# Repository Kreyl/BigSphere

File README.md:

# BigSphere
Hardware for big shining sphere with 70 bright LEDs

To create effects use https://github.com/notiel/SphereUI
Change arrays in EffectPulse.h and EffectStrobo.h to generated by effect creator

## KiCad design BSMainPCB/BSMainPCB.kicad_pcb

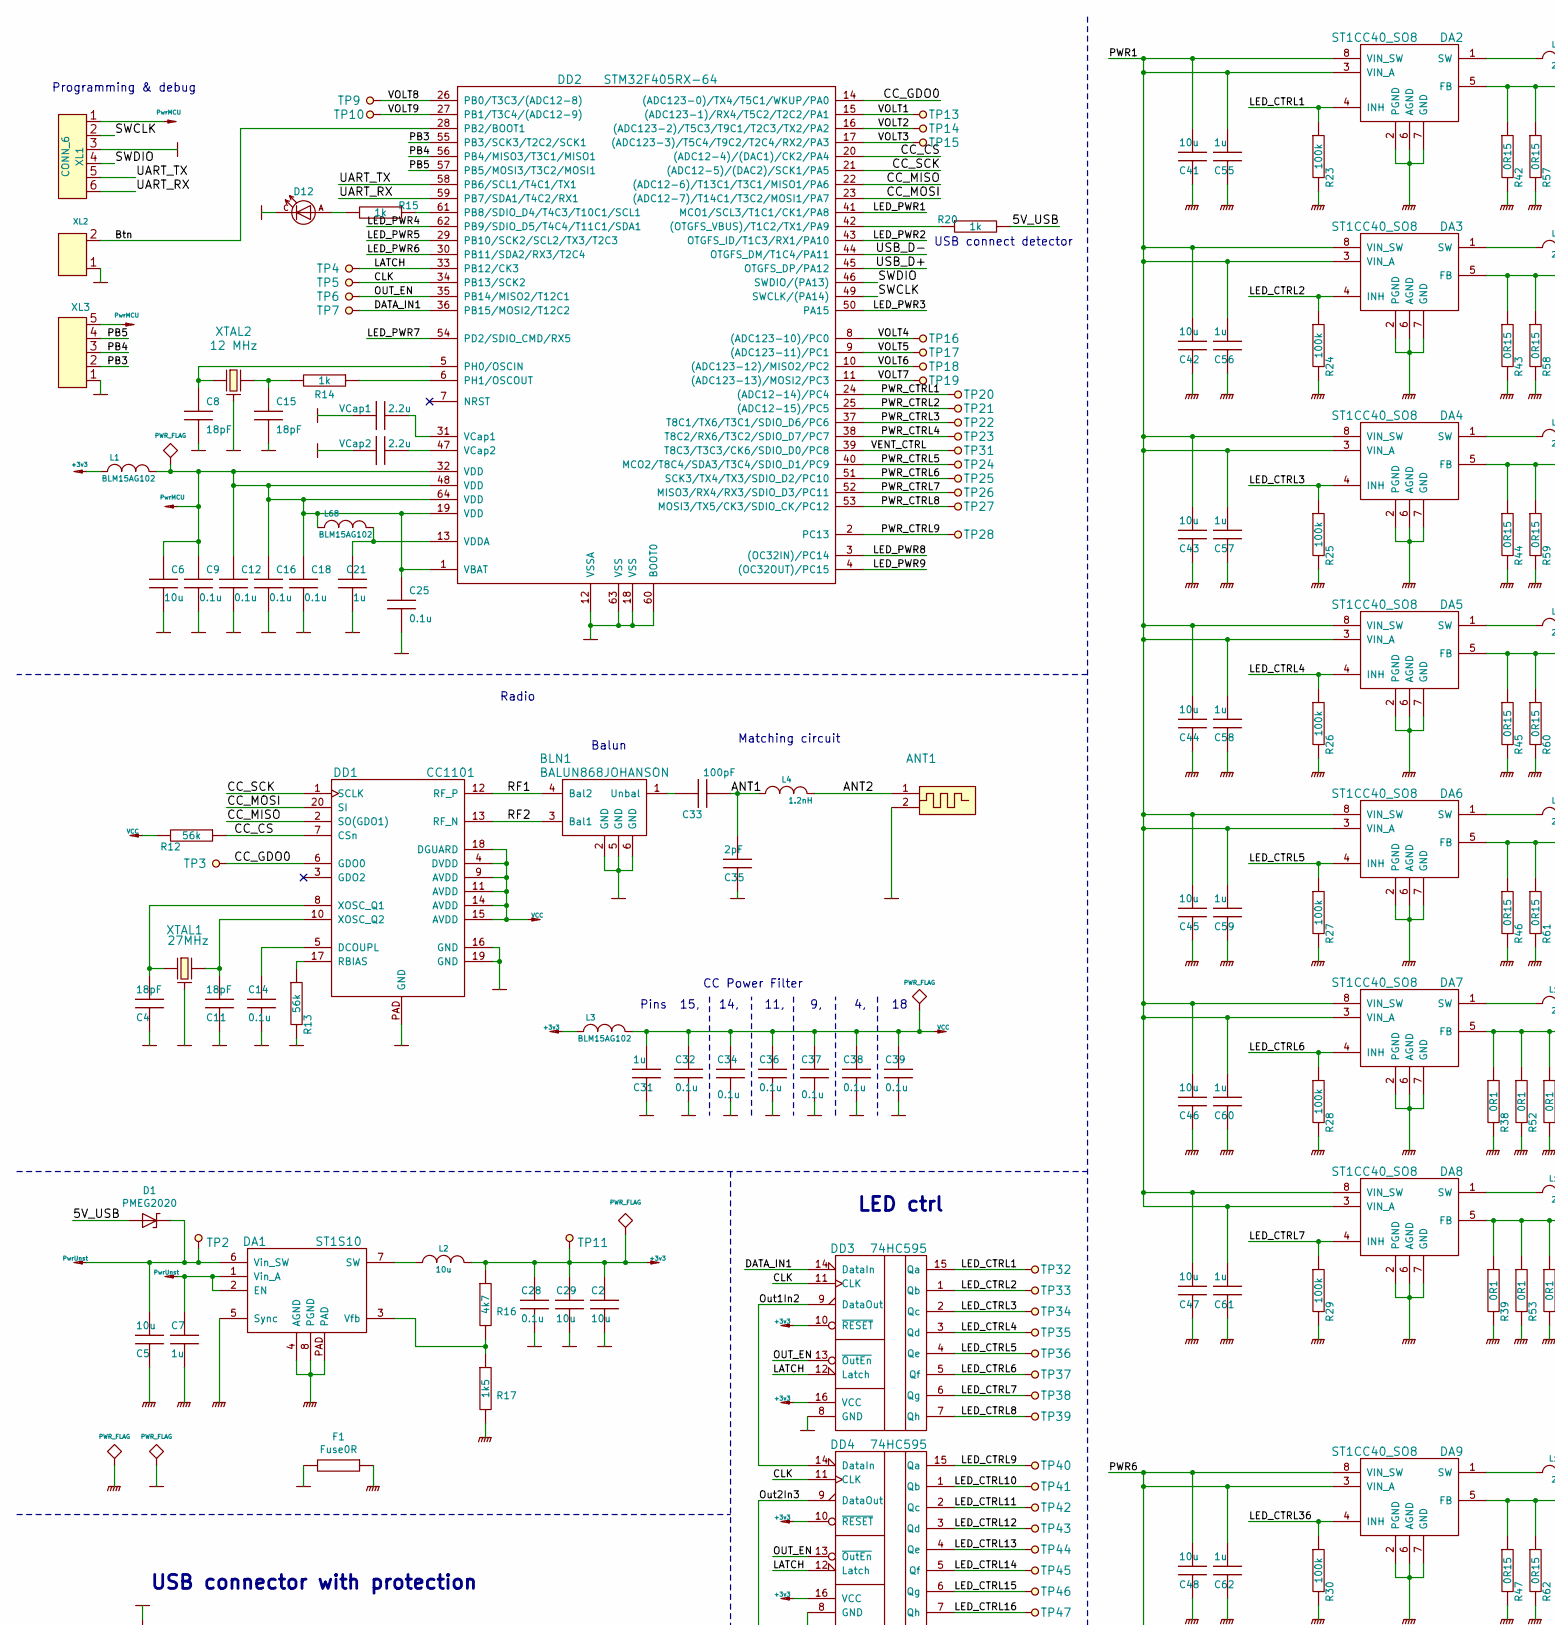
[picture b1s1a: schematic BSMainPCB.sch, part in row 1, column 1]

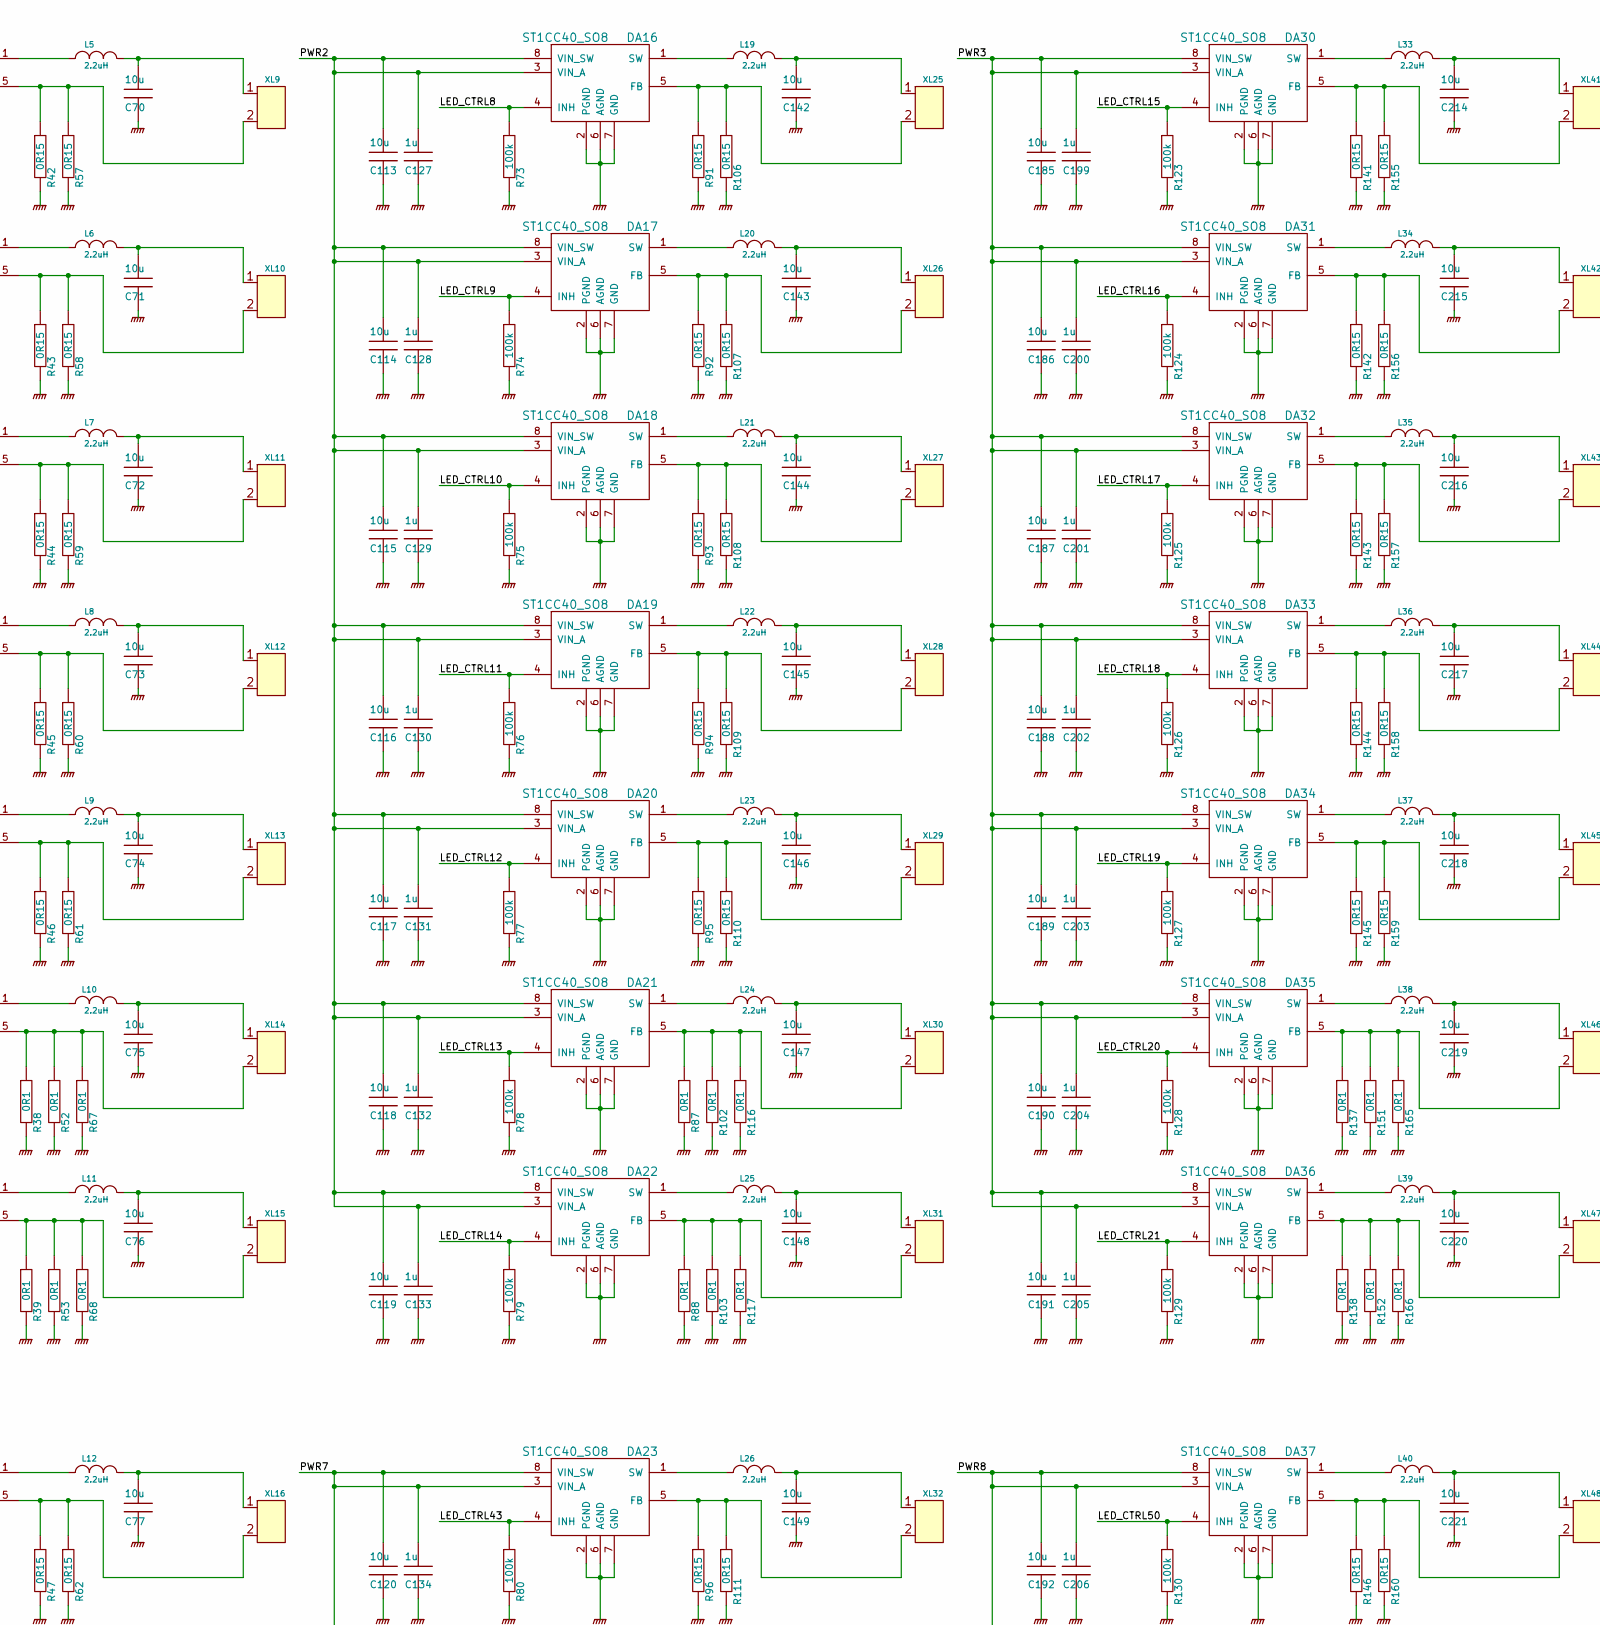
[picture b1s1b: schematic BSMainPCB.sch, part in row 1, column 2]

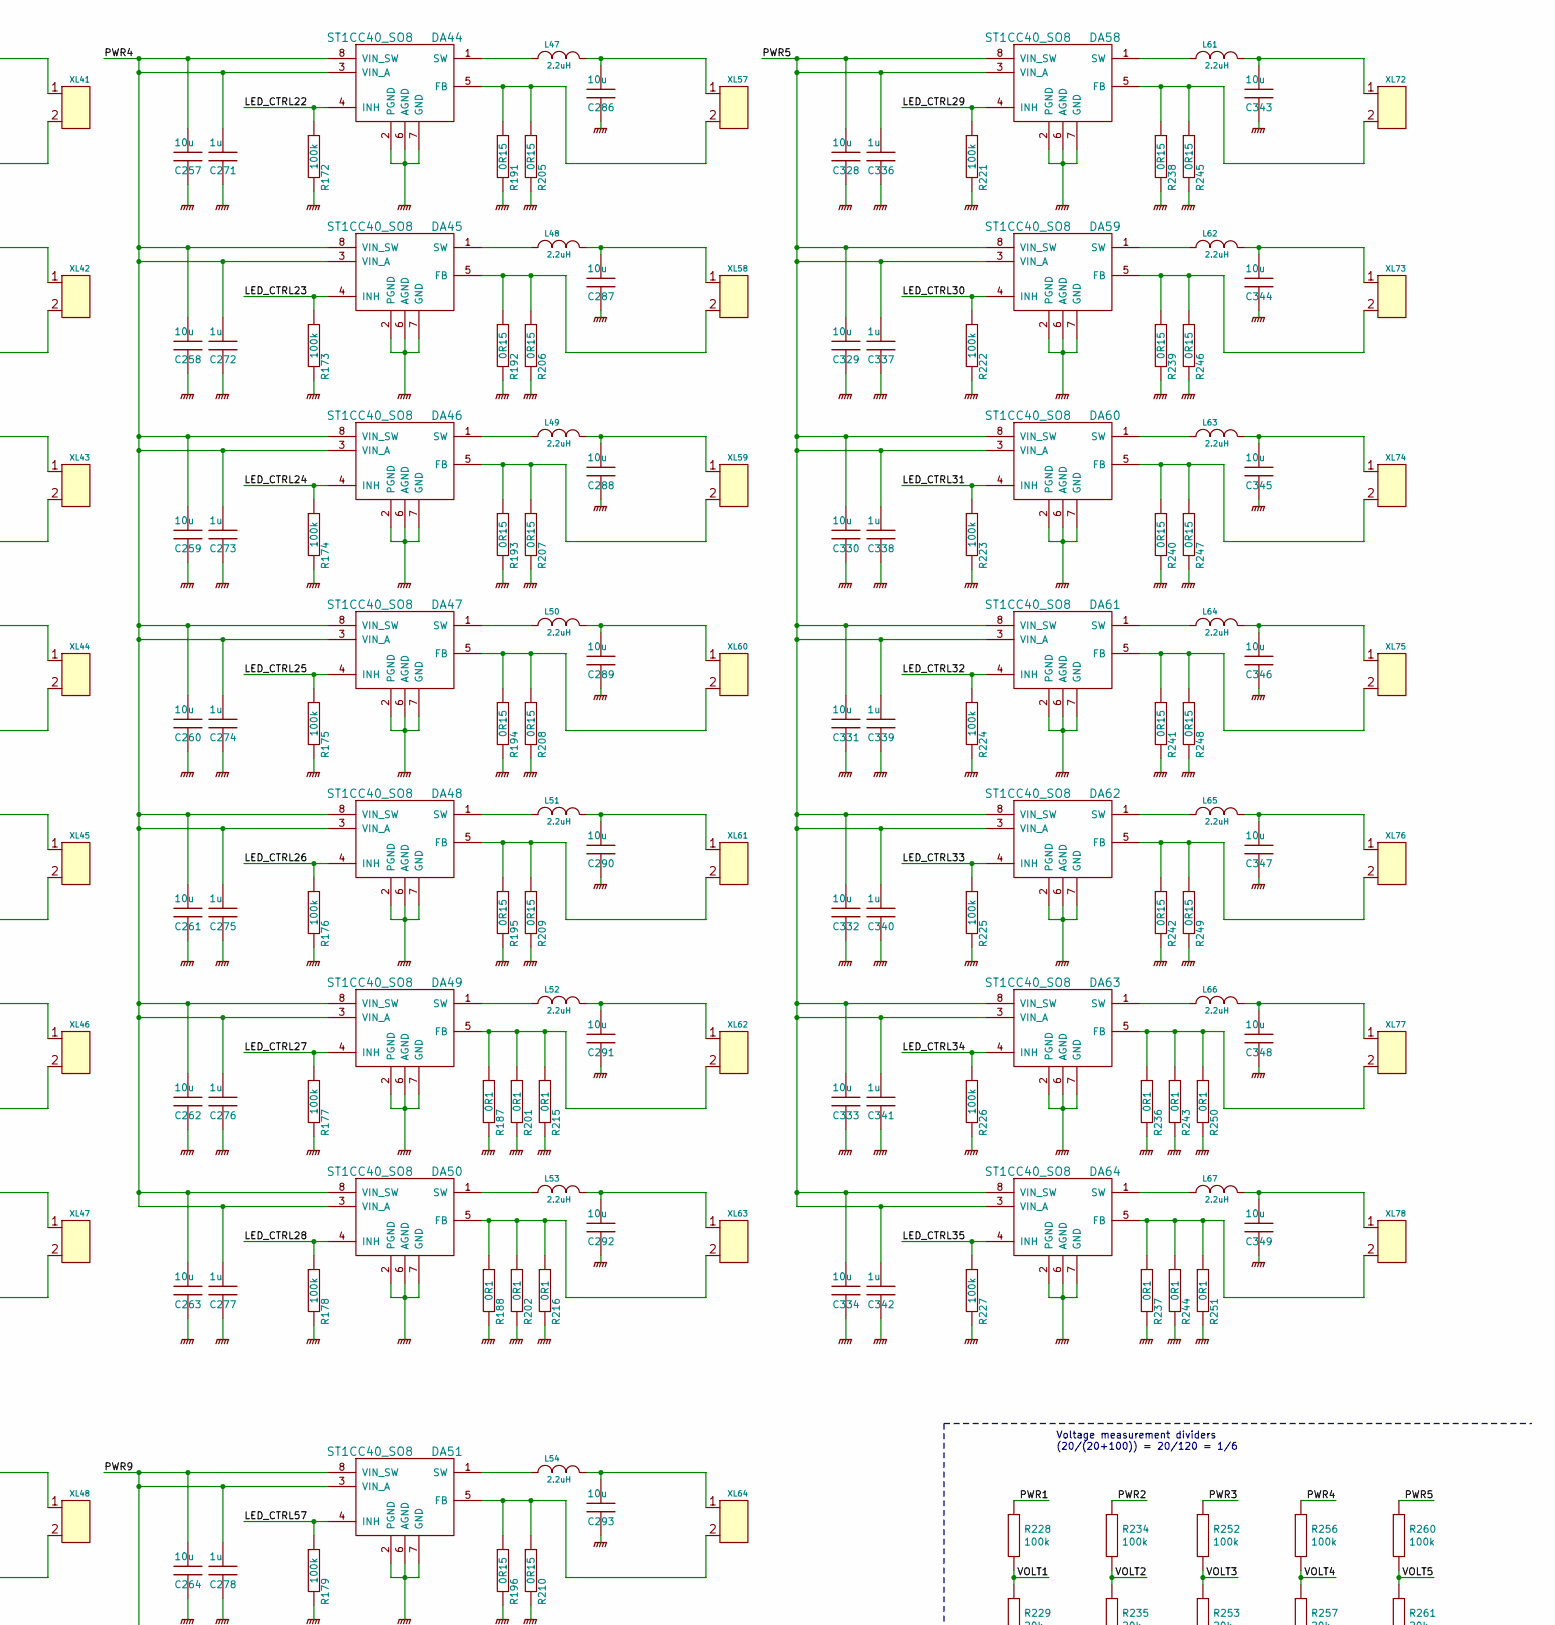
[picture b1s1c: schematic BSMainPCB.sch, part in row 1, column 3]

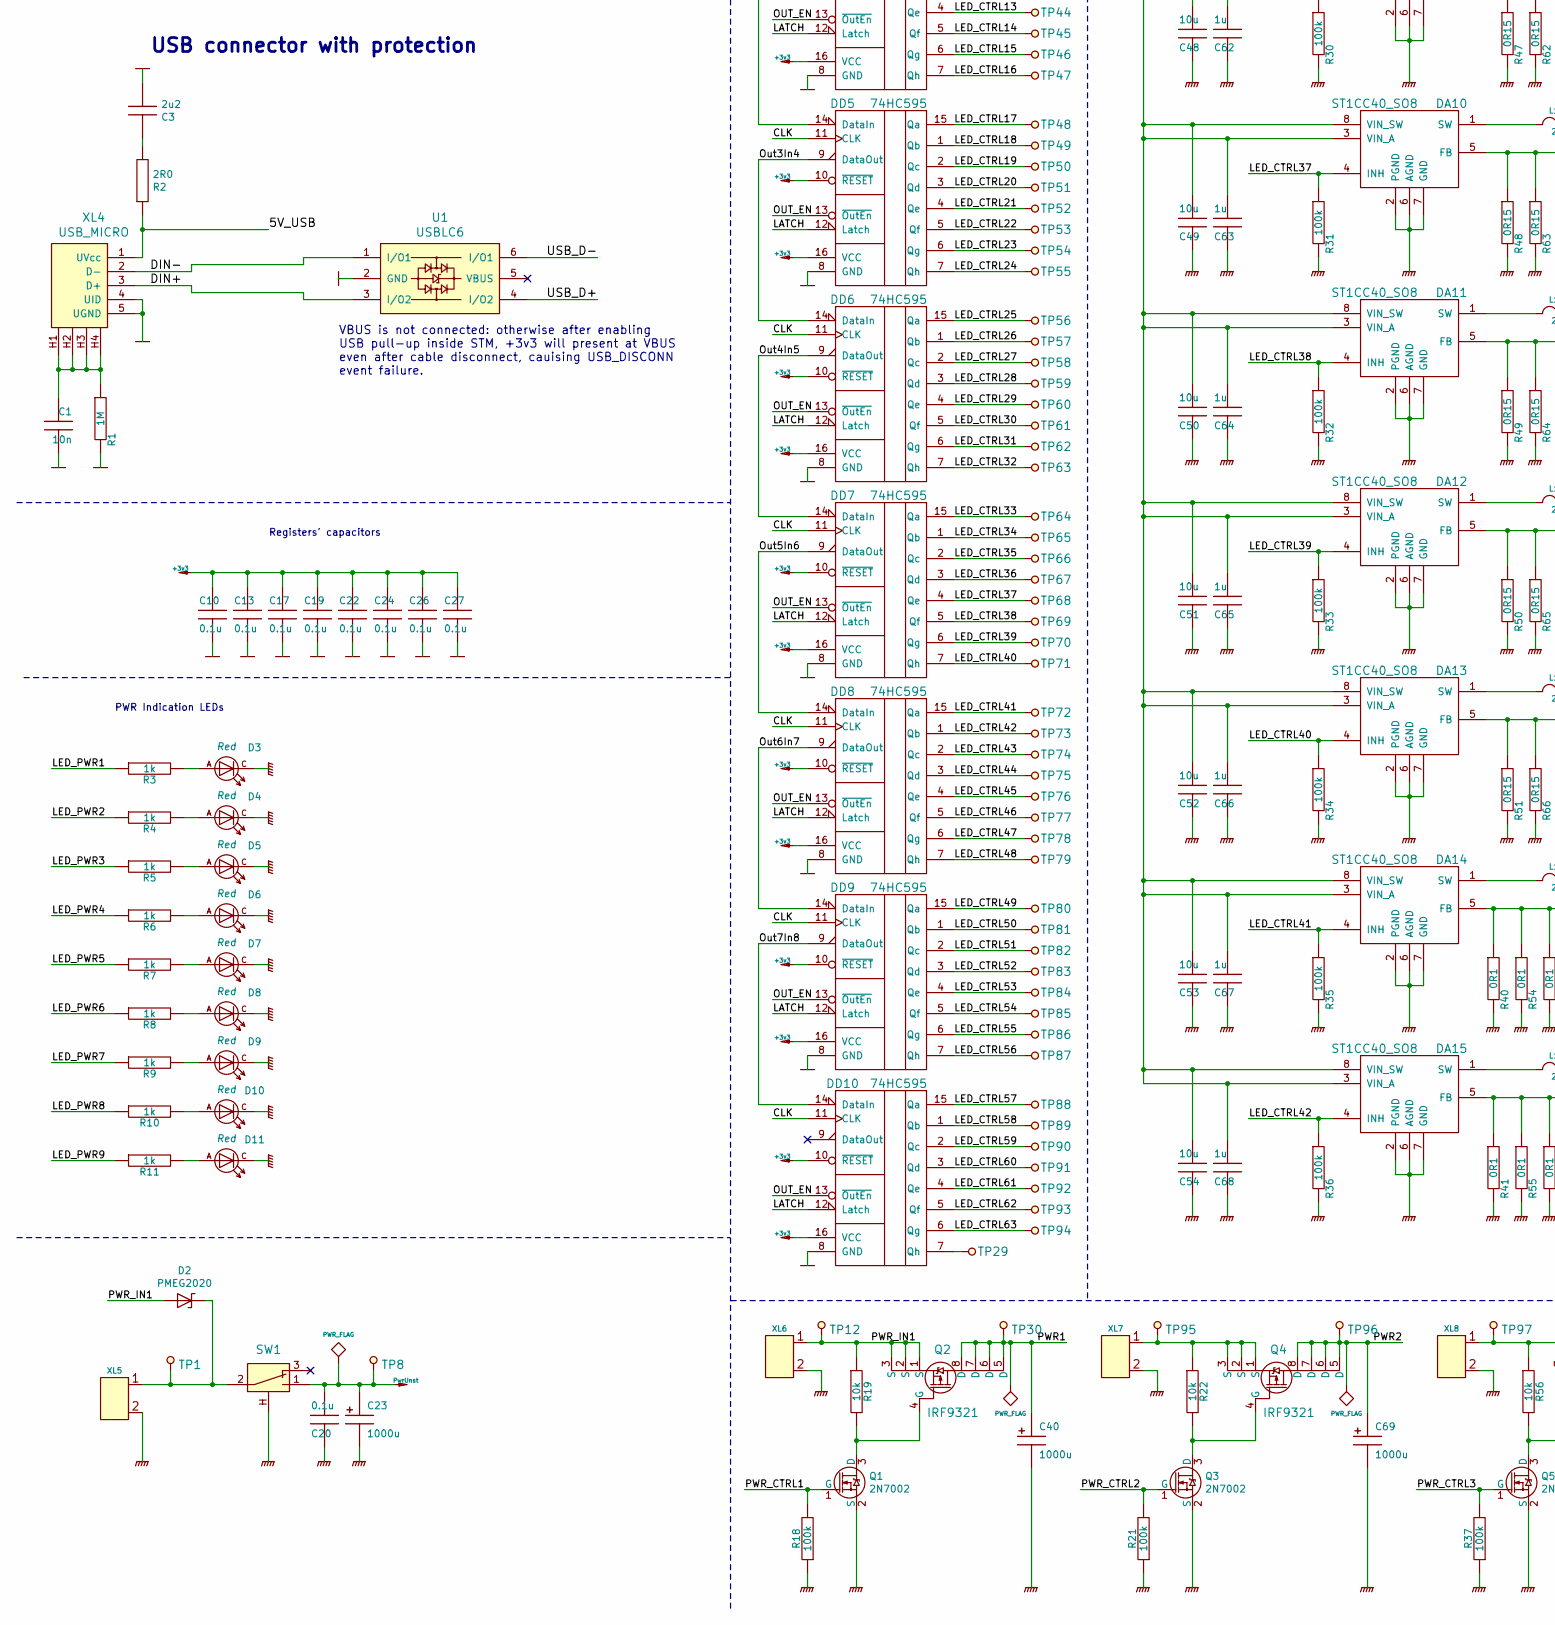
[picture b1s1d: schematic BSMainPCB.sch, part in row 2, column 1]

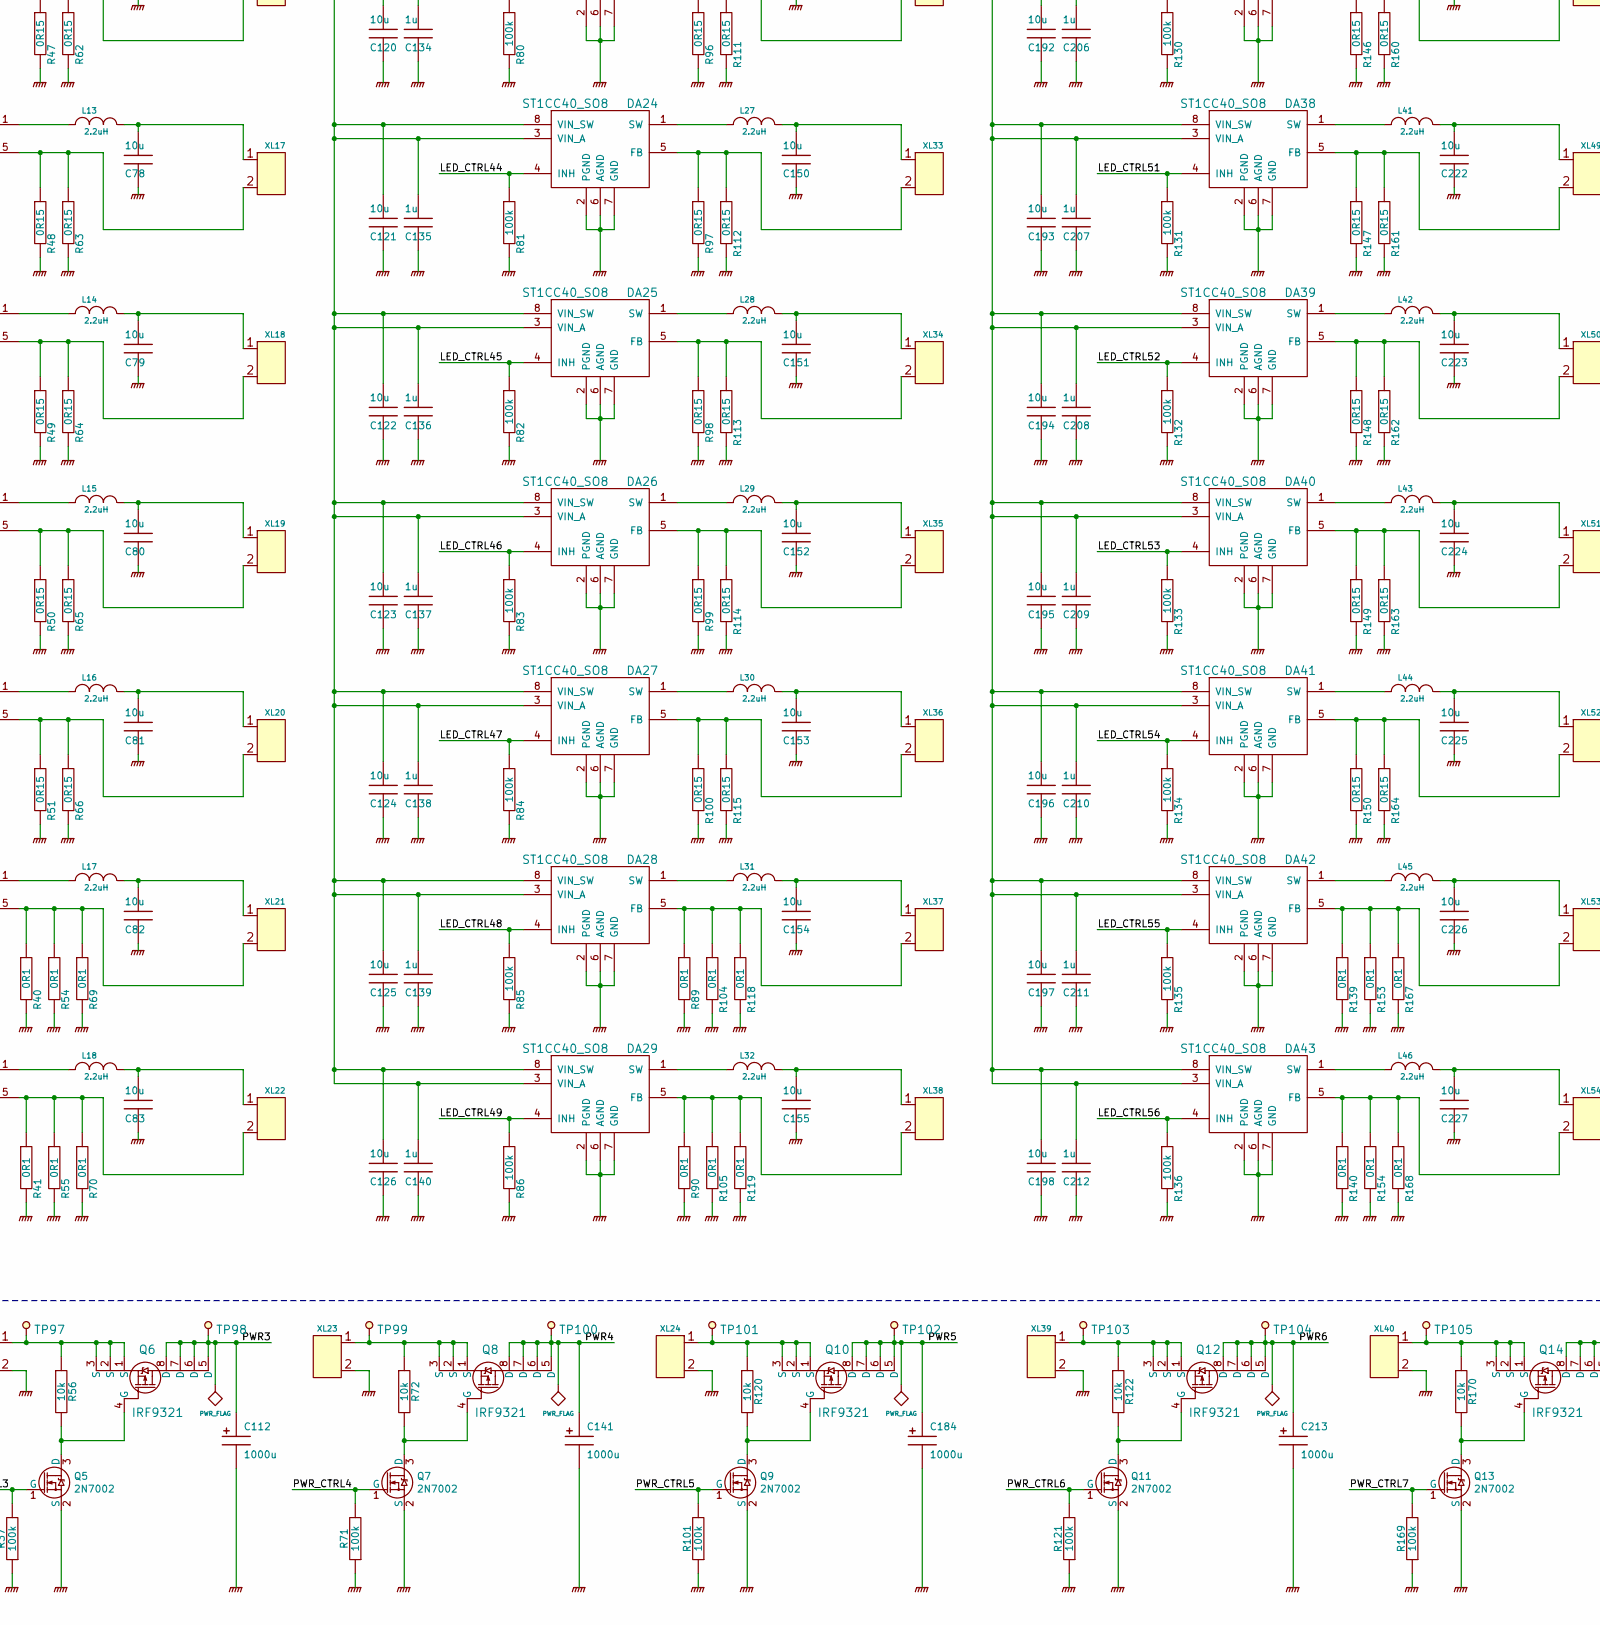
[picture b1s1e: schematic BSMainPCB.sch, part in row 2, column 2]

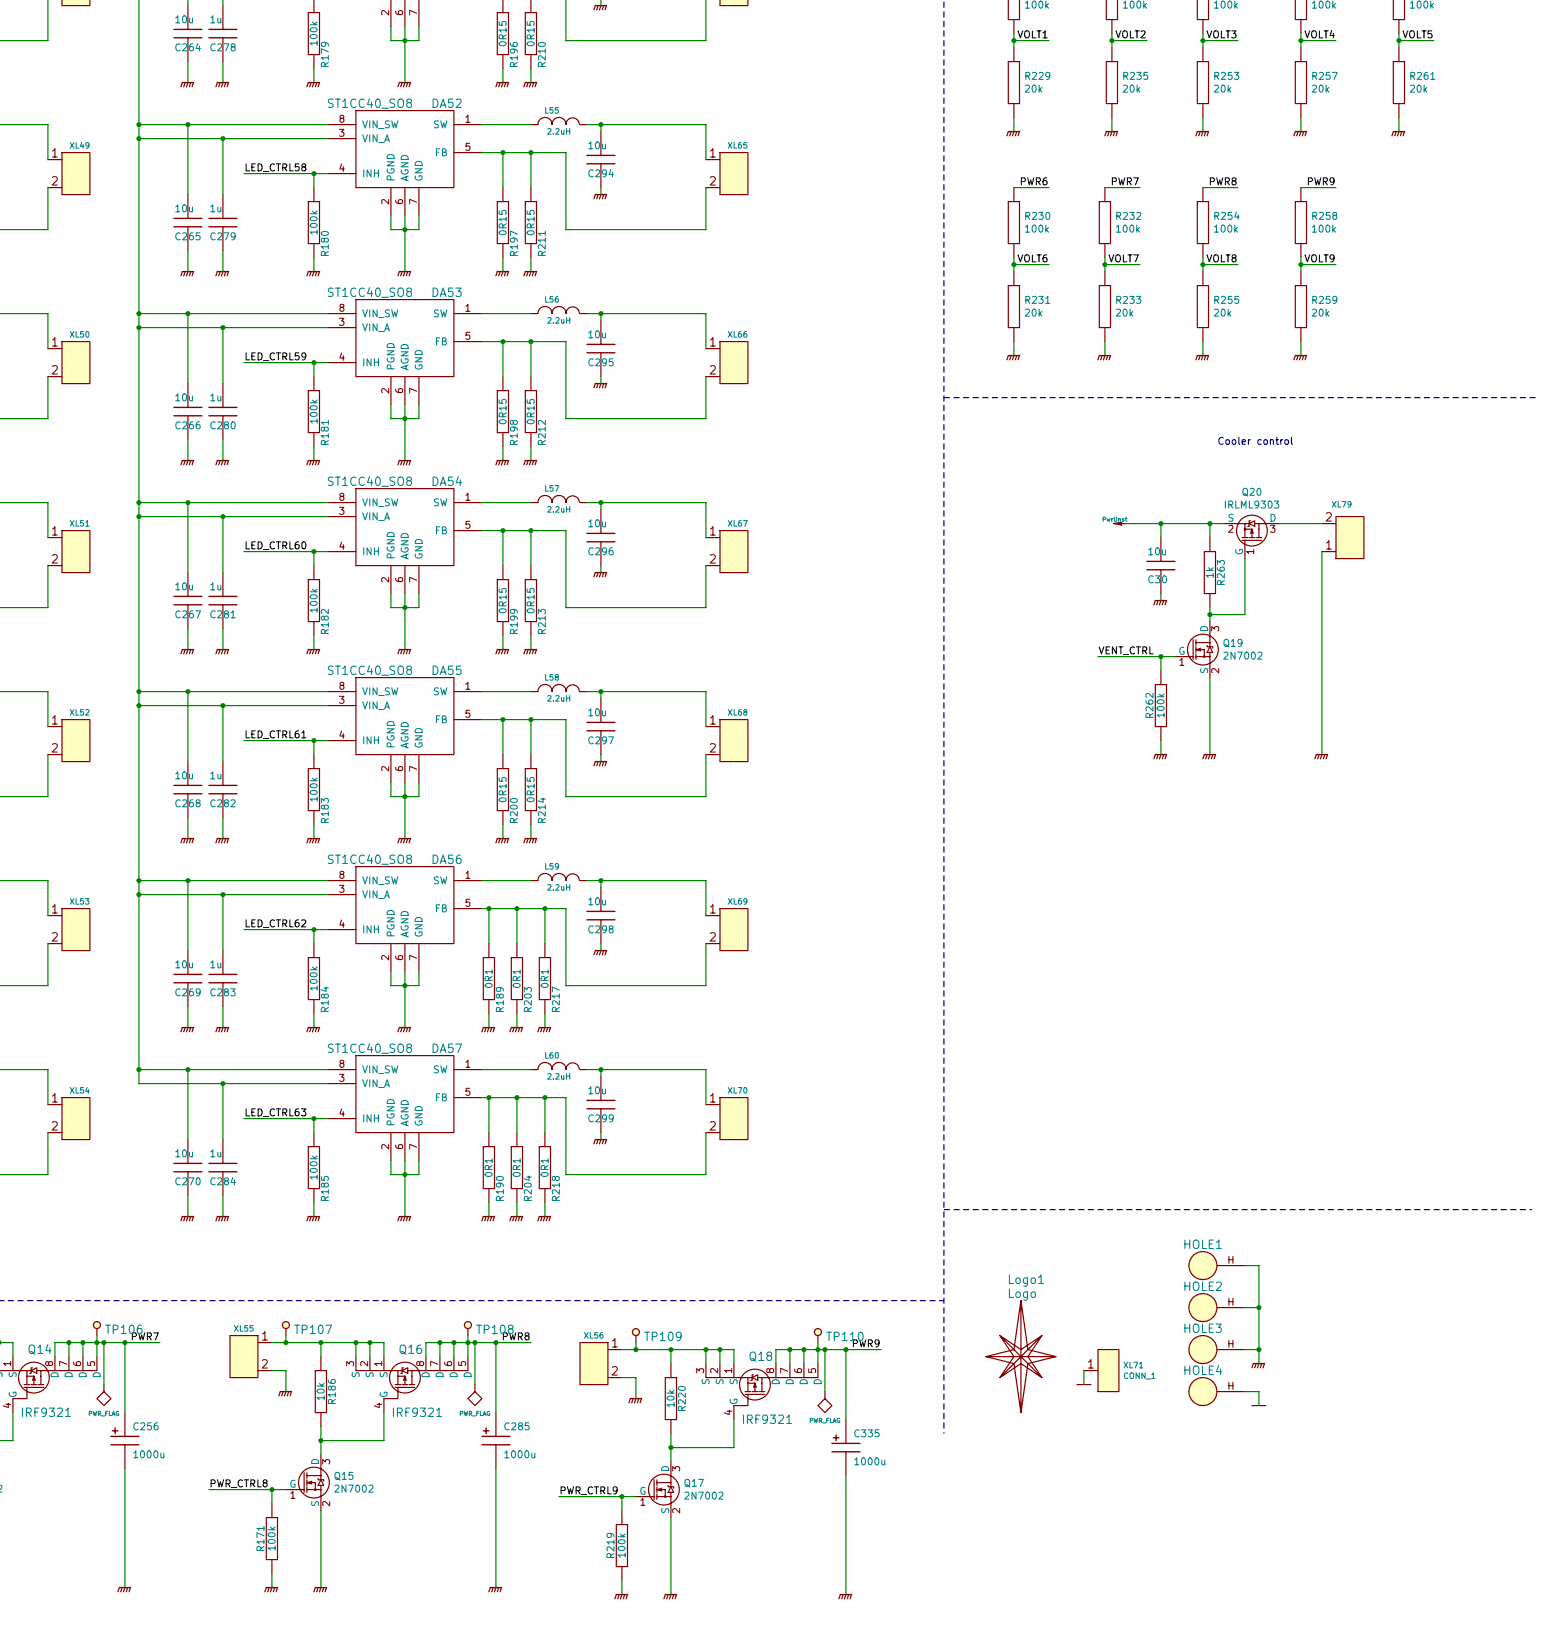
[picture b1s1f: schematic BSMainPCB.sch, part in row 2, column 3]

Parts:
ANT1: ANT_PCB_MONO_2PIN; ANT_868_IFA_SIMPLEJOY_MIRR
BLN1: BALUN868JOHANSON; BALUN_JOHANSON868
C1: 10n; CAP_0603_Silks
C2, C5, C6, C29, C30, C41, C42, C43, C44, C45, C46, C47, C48, C49, C50, C51, C52, C53, C54, C70, C71, C72, C73, C74, C75, C76, C77, C78, C79, C80, C81, C82, C83, C113, C114, C115, C116, C117, C118, C119, C120, C121, C122, C123, C124, C125, C126, C142, C143, C144, C145, C146, C147, C148, C149, C150, C151, C152, C153, C154, C155, C185, C186, C187, C188, C189, C190, C191, C192, C193, C194, C195, C196, C197, C198, C214, C215, C216, C217, C218, C219, C220, C221, C222, C223, C224, C225, C226, C227, C257, C258, C259, C260, C261, C262, C263, C264, C265, C266, C267, C268, C269, C270, C286, C287, C288, C289, C290, C291, C292, C293, C294, C295, C296, C297, C298, C299, C328, C329, C330, C331, C332, C333, C334, C343, C344, C345, C346, C347, C348, C349: 10u; CAP_0805
C3: 2u2; CAP_0603_Silks
C4, C8, C11, C15: 18pF; CAP_0603_Silks
C7, C21, C31, C55, C56, C57, C58, C59, C60, C61, C62, C63, C64, C65, C66, C67, C68, C127, C128, C129, C130, C131, C132, C133, C134, C135, C136, C137, C138, C139, C140, C199, C200, C201, C202, C203, C204, C205, C206, C207, C208, C209, C210, C211, C212, C271, C272, C273, C274, C275, C276, C277, C278, C279, C280, C281, C282, C283, C284, C336, C337, C338, C339, C340, C341, C342: 1u; CAP_0603_Silks
C9, C10, C12, C13, C14, C16, C17, C18, C19, C20, C22, C24, C25, C26, C27, C28, C32, C34, C36, C37, C38, C39: 0.1u; CAP_0603_Silks
C23, C40, C69, C112, C141, C184, C213, C256, C285, C335: 1000u; CAP_10Rx16_HOR
C33: 100pF; CAP_0402
C35: 2pF; CAP_0402
D1, D2: PMEG2020; SOD323
D3, D4, D5, D6, D7, D8, D9, D10, D11: LED; LED_0805
D12: LED; LED_0603
DA1: ST1S10; SO8HEATSINK
DA2, DA3, DA4, DA5, DA6, DA7, DA8, DA9, DA10, DA11, DA12, DA13, DA14, DA15, DA16, DA17, DA18, DA19, DA20, DA21, DA22, DA23, DA24, DA25, DA26, DA27, DA28, DA29, DA30, DA31, DA32, DA33, DA34, DA35, DA36, DA37, DA38, DA39, DA40, DA41, DA42, DA43, DA44, DA45, DA46, DA47, DA48, DA49, DA50, DA51, DA52, DA53, DA54, DA55, DA56, DA57, DA58, DA59, DA60, DA61, DA62, DA63, DA64: ST1CC40_SO8; SO8_150MIL
DD1: CC1101; QFN20
DD2: STM32F405RX-64; LQFP64
DD3, DD4, DD5, DD6, DD7, DD8, DD9, DD10: 74HC595; SO16_150MIL
F1: Fuse0R; FuseShorted
HOLE1, HOLE2, HOLE3, HOLE4: HOLE_METALLED; Hole3_5_out6mm
L1, L3, L68: BLM15AG102; IND_0402
L2: 10u; SDR0604
L4: 1.2nH; IND_0402
L5, L6, L7, L8, L9, L10, L11, L12, L13, L14, L15, L16, L17, L18, L19, L20, L21, L22, L23, L24, L25, L26, L27, L28, L29, L30, L31, L32, L33, L34, L35, L36, L37, L38, L39, L40, L41, L42, L43, L44, L45, L46, L47, L48, L49, L50, L51, L52, L53, L54, L55, L56, L57, L58, L59, L60, L61, L62, L63, L64, L65, L66, L67: 2.2uH; IND_SRN2512
Logo1: Logo; Ostranna_12d7_10d1
Q1, Q3, Q5, Q7, Q9, Q11, Q13, Q15, Q17, Q19: 2N7002; SOT23-3
Q2, Q4, Q6, Q8, Q10, Q12, Q14, Q16, Q18: IRF9321; SO8HEATSINK
Q20: IRLML9303; SOT23-3
R1: 1M; RES_0603
R2: 2R0; RES_0603
R3, R4, R5, R6, R7, R8, R9, R10, R11, R14, R15, R20, R263: 1k; RES_0603
R12, R13: 56k; RES_0603
R16: 4k7; RES_0603
R17: 1k5; RES_0603
R18, R21, R23, R24, R25, R26, R27, R28, R29, R30, R31, R32, R33, R34, R35, R36, R37, R71, R73, R74, R75, R76, R77, R78, R79, R80, R81, R82, R83, R84, R85, R86, R101, R121, R123, R124, R125, R126, R127, R128, R129, R130, R131, R132, R133, R134, R135, R136, R169, R171, R172, R173, R174, R175, R176, R177, R178, R179, R180, R181, R182, R183, R184, R185, R219, R221, R222, R223, R224, R225, R226, R227, R228, R230, R232, R234, R252, R254, R256, R258, R260, R262: 100k; RES_0603
R19, R22, R56, R72, R120, R122, R170, R186, R220: 10k; RES_0603
R38, R39, R40, R41, R52, R53, R54, R55, R67, R68, R69, R70, R87, R88, R89, R90, R102, R103, R104, R105, R116, R117, R118, R119, R137, R138, R139, R140, R151, R152, R153, R154, R165, R166, R167, R168, R187, R188, R189, R190, R201, R202, R203, R204, R215, R216, R217, R218, R236, R237, R243, R244, R250, R251: 0R1; RES_1206
R42, R43, R44, R45, R46, R47, R48, R49, R50, R51, R57, R58, R59, R60, R61, R62, R63, R64, R65, R66, R91, R92, R93, R94, R95, R96, R97, R98, R99, R100, R106, R107, R108, R109, R110, R111, R112, R113, R114, R115, R141, R142, R143, R144, R145, R146, R147, R148, R149, R150, R155, R156, R157, R158, R159, R160, R161, R162, R163, R164, R191, R192, R193, R194, R195, R196, R197, R198, R199, R200, R205, R206, R207, R208, R209, R210, R211, R212, R213, R214, R238, R239, R240, R241, R242, R245, R246, R247, R248, R249: 0R15; RES_1206
R229, R231, R233, R235, R253, R255, R257, R259, R261: 20k; RES_0603
SW1: SWITCH_H; SW_SS9
TP1, TP2, TP3, TP4, TP5, TP6, TP7, TP8, TP9, TP10, TP11, TP12, TP13, TP14, TP15, TP16, TP17, TP18, TP19, TP20, TP21, TP22, TP23, TP24, TP25, TP26, TP27, TP28, TP29, TP30, TP31, TP32, TP33, TP34, TP35, TP36, TP37, TP38, TP39, TP40, TP41, TP42, TP43, TP44, TP45, TP46, TP47, TP48, TP49, TP50, TP51, TP52, TP53, TP54, TP55, TP56, TP57, TP58, TP59, TP60, TP61, TP62, TP63, TP64, TP65, TP66, TP67, TP68, TP69, TP70, TP71, TP72, TP73, TP74, TP75, TP76, TP77, TP78, TP79, TP80, TP81, TP82, TP83, TP84, TP85, TP86, TP87, TP88, TP89, TP90, TP91, TP92, TP93, TP94, TP95, TP96, TP97, TP98, TP99, TP100, TP101, TP102, TP103, TP104, TP105, TP106, TP107, TP108, TP109, TP110: TESTPOINT; TESTPOINT_1MM
U1: USBLC6; SOT23-6
VCap1, VCap2: 2.2u; CAP_0603
XL1: CONN_6; PLS-6_LOCK
XL2: CONN_2; WB-02(MW-2M)
XL3: CONN_5; PLS-5
XL4: USB_MICRO; USBmicro_MOLEX_1050170001
XL5, XL6, XL7, XL8, XL23, XL24, XL39, XL40, XL55, XL56: CONN_2; 2ZHDRC-02P
XL9, XL10, XL11, XL12, XL13, XL14, XL15, XL16, XL17, XL18, XL19, XL20, XL21, XL22, XL25, XL26, XL27, XL28, XL29, XL30, XL31, XL32, XL33, XL34, XL35, XL36, XL37, XL38, XL41, XL42, XL43, XL44, XL45, XL46, XL47, XL48, XL49, XL50, XL51, XL52, XL53, XL54, XL57, XL58, XL59, XL60, XL61, XL62, XL63, XL64, XL65, XL66, XL67, XL68, XL69, XL70, XL72, XL73, XL74, XL75, XL76, XL77, XL78: CONN_2; Oval3x1.5wHole0d9_x2
XL71: CONN_1; PLS-1Rnd
XL79: CONN_2; W02_Pitch_2d54
XTAL1: 27MHz; 03225C4
XTAL2: 12 MHz; 03225C4

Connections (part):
+3v3: C2.2, C10.2, C13.2, C17.2, C19.2, C22.2, C24.2, C26.2, C27.2, C28.2, C29.2, DD3.10 (~RESET), DD3.16 (VCC), DD4.10 (~RESET), DD4.16 (VCC), DD5.10 (~RESET), DD5.16 (VCC), DD6.10 (~RESET), DD6.16 (VCC), DD7.10 (~RESET), DD7.16 (VCC), DD8.10 (~RESET), DD8.16 (VCC), DD9.10 (~RESET), DD9.16 (VCC), DD10.10 (~RESET), DD10.16 (VCC), L1.2, L2.1, L3.2, R16.1, TP11.1
/5V_USB: D1.A, R2.1, R20.2, XL4.1 (UVcc)
/ANT1: C33.1, C35.1, L4.2
/ANT2: ANT1.1, L4.1
/Btn: DD2.28 (PB2/BOOT1), XL2.2 (PM)
/CC_CS: DD1.7 (CSn), DD2.20 ((ADC12-4)/(DAC1)/CK2/PA4), R12.1
/CC_GDO0: DD1.6 (GDO0), DD2.14 ((ADC123-0)/TX4/T5C1/WKUP/PA0), TP3.1
/CC_MISO: DD1.2 (SO(GDO1)), DD2.22 ((ADC12-6)/T13C1/T3C1/MISO1/PA6)
/CC_MOSI: DD1.20 (SI), DD2.23 ((ADC12-7)/T14C1/T3C2/MOSI1/PA7)
/CC_SCK: DD1.1 (SCLK), DD2.21 ((ADC12-5)/(DAC2)/SCK1/PA5)
/CLK: DD2.34 (PB13/SCK2), DD3.11 (CLK), DD4.11 (CLK), DD5.11 (CLK), DD6.11 (CLK), DD7.11 (CLK), DD8.11 (CLK), DD9.11 (CLK), DD10.11 (CLK), TP5.1
/DATA_IN1: DD2.36 (PB15/MOSI2/T12C2), DD3.14 (DataIn), TP7.1
/DIN+: U1.3 (I/O2), XL4.3 (D+)
/DIN-: U1.1 (I/O1), XL4.2 (D-)
/LATCH: DD2.33 (PB12/CK3), DD3.12 (Latch), DD4.12 (Latch), DD5.12 (Latch), DD6.12 (Latch), DD7.12 (Latch), DD8.12 (Latch), DD9.12 (Latch), DD10.12 (Latch), TP4.1
/LED_CTRL1: DA2.4 (INH), DD3.15 (Qa), R23.1, TP32.1
/LED_CTRL2: DA3.4 (INH), DD3.1 (Qb), R24.1, TP33.1
/LED_CTRL3: DA4.4 (INH), DD3.2 (Qc), R25.1, TP34.1
/LED_CTRL4: DA5.4 (INH), DD3.3 (Qd), R26.1, TP35.1
/LED_CTRL5: DA6.4 (INH), DD3.4 (Qe), R27.1, TP36.1
/LED_CTRL6: DA7.4 (INH), DD3.5 (Qf), R28.1, TP37.1
/LED_CTRL7: DA8.4 (INH), DD3.6 (Qg), R29.1, TP38.1
/LED_CTRL8: DA16.4 (INH), DD3.7 (Qh), R73.1, TP39.1
/LED_CTRL9: DA17.4 (INH), DD4.15 (Qa), R74.1, TP40.1
/LED_CTRL10: DA18.4 (INH), DD4.1 (Qb), R75.1, TP41.1
/LED_CTRL11: DA19.4 (INH), DD4.2 (Qc), R76.1, TP42.1
/LED_CTRL12: DA20.4 (INH), DD4.3 (Qd), R77.1, TP43.1
/LED_CTRL13: DA21.4 (INH), DD4.4 (Qe), R78.1, TP44.1
/LED_CTRL14: DA22.4 (INH), DD4.5 (Qf), R79.1, TP45.1
/LED_CTRL15: DA30.4 (INH), DD4.6 (Qg), R123.1, TP46.1
/LED_CTRL16: DA31.4 (INH), DD4.7 (Qh), R124.1, TP47.1
/LED_CTRL17: DA32.4 (INH), DD5.15 (Qa), R125.1, TP48.1
/LED_CTRL18: DA33.4 (INH), DD5.1 (Qb), R126.1, TP49.1
/LED_CTRL19: DA34.4 (INH), DD5.2 (Qc), R127.1, TP50.1
/LED_CTRL20: DA35.4 (INH), DD5.3 (Qd), R128.1, TP51.1
/LED_CTRL21: DA36.4 (INH), DD5.4 (Qe), R129.1, TP52.1
/LED_CTRL22: DA44.4 (INH), DD5.5 (Qf), R172.1, TP53.1
/LED_CTRL23: DA45.4 (INH), DD5.6 (Qg), R173.1, TP54.1
/LED_CTRL24: DA46.4 (INH), DD5.7 (Qh), R174.1, TP55.1
/LED_CTRL25: DA47.4 (INH), DD6.15 (Qa), R175.1, TP56.1
/LED_CTRL26: DA48.4 (INH), DD6.1 (Qb), R176.1, TP57.1
/LED_CTRL27: DA49.4 (INH), DD6.2 (Qc), R177.1, TP58.1
/LED_CTRL28: DA50.4 (INH), DD6.3 (Qd), R178.1, TP59.1
/LED_CTRL29: DA58.4 (INH), DD6.4 (Qe), R221.1, TP60.1
/LED_CTRL30: DA59.4 (INH), DD6.5 (Qf), R222.1, TP61.1
/LED_CTRL31: DA60.4 (INH), DD6.6 (Qg), R223.1, TP62.1
/LED_CTRL32: DA61.4 (INH), DD6.7 (Qh), R224.1, TP63.1
/LED_CTRL33: DA62.4 (INH), DD7.15 (Qa), R225.1, TP64.1
/LED_CTRL34: DA63.4 (INH), DD7.1 (Qb), R226.1, TP65.1
/LED_CTRL35: DA64.4 (INH), DD7.2 (Qc), R227.1, TP66.1
/LED_CTRL36: DA9.4 (INH), DD7.3 (Qd), R30.1, TP67.1
/LED_CTRL37: DA10.4 (INH), DD7.4 (Qe), R31.1, TP68.1
/LED_CTRL38: DA11.4 (INH), DD7.5 (Qf), R32.1, TP69.1
/LED_CTRL39: DA12.4 (INH), DD7.6 (Qg), R33.1, TP70.1
/LED_CTRL40: DA13.4 (INH), DD7.7 (Qh), R34.1, TP71.1
/LED_CTRL41: DA14.4 (INH), DD8.15 (Qa), R35.1, TP72.1
/LED_CTRL42: DA15.4 (INH), DD8.1 (Qb), R36.1, TP73.1
/LED_CTRL43: DA23.4 (INH), DD8.2 (Qc), R80.1, TP74.1
/LED_CTRL44: DA24.4 (INH), DD8.3 (Qd), R81.1, TP75.1
/LED_CTRL45: DA25.4 (INH), DD8.4 (Qe), R82.1, TP76.1
/LED_CTRL46: DA26.4 (INH), DD8.5 (Qf), R83.1, TP77.1
/LED_CTRL47: DA27.4 (INH), DD8.6 (Qg), R84.1, TP78.1
/LED_CTRL48: DA28.4 (INH), DD8.7 (Qh), R85.1, TP79.1
/LED_CTRL49: DA29.4 (INH), DD9.15 (Qa), R86.1, TP80.1
/LED_CTRL50: DA37.4 (INH), DD9.1 (Qb), R130.1, TP81.1
/LED_CTRL51: DA38.4 (INH), DD9.2 (Qc), R131.1, TP82.1
/LED_CTRL52: DA39.4 (INH), DD9.3 (Qd), R132.1, TP83.1
/LED_CTRL53: DA40.4 (INH), DD9.4 (Qe), R133.1, TP84.1
/LED_CTRL54: DA41.4 (INH), DD9.5 (Qf), R134.1, TP85.1
/LED_CTRL55: DA42.4 (INH), DD9.6 (Qg), R135.1, TP86.1
/LED_CTRL56: DA43.4 (INH), DD9.7 (Qh), R136.1, TP87.1
/LED_CTRL57: DA51.4 (INH), DD10.15 (Qa), R179.1, TP88.1
/LED_CTRL58: DA52.4 (INH), DD10.1 (Qb), R180.1, TP89.1
/LED_CTRL59: DA53.4 (INH), DD10.2 (Qc), R181.1, TP90.1
/LED_CTRL60: DA54.4 (INH), DD10.3 (Qd), R182.1, TP91.1
/LED_CTRL61: DA55.4 (INH), DD10.4 (Qe), R183.1, TP92.1
/LED_CTRL62: DA56.4 (INH), DD10.5 (Qf), R184.1, TP93.1
/LED_CTRL63: DA57.4 (INH), DD10.6 (Qg), R185.1, TP94.1
/LED_PWR1: DD2.41 (MCO1/SCL3/T1C1/CK1/PA8), R3.1
/LED_PWR2: DD2.43 (OTGFS_ID/T1C3/RX1/PA10), R4.1
/LED_PWR3: DD2.50 (PA15), R5.1
/LED_PWR4: DD2.62 (PB9/SDIO_D5/T4C4/T11C1/SDA1), R6.1
/LED_PWR5: DD2.29 (PB10/SCK2/SCL2/TX3/T2C3), R7.1
/LED_PWR6: DD2.30 (PB11/SDA2/RX3/T2C4), R8.1
/LED_PWR7: DD2.54 (PD2/SDIO_CMD/RX5), R9.1
/LED_PWR8: DD2.3 ((OC32IN)/PC14), R10.1
/LED_PWR9: DD2.4 ((OC32OUT)/PC15), R11.1
/OUT_EN: DD2.35 (PB14/MISO2/T12C1), DD3.13 (~OutEn), DD4.13 (~OutEn), DD5.13 (~OutEn), DD6.13 (~OutEn), DD7.13 (~OutEn), DD8.13 (~OutEn), DD9.13 (~OutEn), DD10.13 (~OutEn), TP6.1
/Out1In2: DD3.9 (DataOut), DD4.14 (DataIn)
/Out2In3: DD4.9 (DataOut), DD5.14 (DataIn)
/Out3In4: DD5.9 (DataOut), DD6.14 (DataIn)
/Out4In5: DD6.9 (DataOut), DD7.14 (DataIn)
/Out5In6: DD7.9 (DataOut), DD8.14 (DataIn)
/Out6In7: DD8.9 (DataOut), DD9.14 (DataIn)
/Out7In8: DD9.9 (DataOut), DD10.14 (DataIn)
/PB3: DD2.55 (PB3/SCK3/T2C2/SCK1), XL3.2
/PB4: DD2.56 (PB4/MISO3/T3C1/MISO1), XL3.3
/PB5: DD2.57 (PB5/MOSI3/T3C2/MOSI1), XL3.4
/PWR1: C40.1, C41.1, C42.1, C43.1, C44.1, C45.1, C46.1, C47.1, C55.1, C56.1, C57.1, C58.1, C59.1, C60.1, C61.1, DA2.3 (VIN_A), DA2.8 (VIN_SW), DA3.3 (VIN_A), DA3.8 (VIN_SW), DA4.3 (VIN_A), DA4.8 (VIN_SW), DA5.3 (VIN_A), DA5.8 (VIN_SW), DA6.3 (VIN_A), DA6.8 (VIN_SW), DA7.3 (VIN_A), DA7.8 (VIN_SW), DA8.3 (VIN_A), DA8.8 (VIN_SW), Q2.5 (D), Q2.6 (D), Q2.7 (D), Q2.8 (D), R228.1, TP30.1
/PWR2: C69.1, C113.1, C114.1, C115.1, C116.1, C117.1, C118.1, C119.1, C127.1, C128.1, C129.1, C130.1, C131.1, C132.1, C133.1, DA16.3 (VIN_A), DA16.8 (VIN_SW), DA17.3 (VIN_A), DA17.8 (VIN_SW), DA18.3 (VIN_A), DA18.8 (VIN_SW), DA19.3 (VIN_A), DA19.8 (VIN_SW), DA20.3 (VIN_A), DA20.8 (VIN_SW), DA21.3 (VIN_A), DA21.8 (VIN_SW), DA22.3 (VIN_A), DA22.8 (VIN_SW), Q4.5 (D), Q4.6 (D), Q4.7 (D), Q4.8 (D), R234.1, TP96.1
/PWR3: C112.1, C185.1, C186.1, C187.1, C188.1, C189.1, C190.1, C191.1, C199.1, C200.1, C201.1, C202.1, C203.1, C204.1, C205.1, DA30.3 (VIN_A), DA30.8 (VIN_SW), DA31.3 (VIN_A), DA31.8 (VIN_SW), DA32.3 (VIN_A), DA32.8 (VIN_SW), DA33.3 (VIN_A), DA33.8 (VIN_SW), DA34.3 (VIN_A), DA34.8 (VIN_SW), DA35.3 (VIN_A), DA35.8 (VIN_SW), DA36.3 (VIN_A), DA36.8 (VIN_SW), Q6.5 (D), Q6.6 (D), Q6.7 (D), Q6.8 (D), R252.1, TP98.1
/PWR4: C141.1, C257.1, C258.1, C259.1, C260.1, C261.1, C262.1, C263.1, C271.1, C272.1, C273.1, C274.1, C275.1, C276.1, C277.1, DA44.3 (VIN_A), DA44.8 (VIN_SW), DA45.3 (VIN_A), DA45.8 (VIN_SW), DA46.3 (VIN_A), DA46.8 (VIN_SW), DA47.3 (VIN_A), DA47.8 (VIN_SW), DA48.3 (VIN_A), DA48.8 (VIN_SW), DA49.3 (VIN_A), DA49.8 (VIN_SW), DA50.3 (VIN_A), DA50.8 (VIN_SW), Q8.5 (D), Q8.6 (D), Q8.7 (D), Q8.8 (D), R256.1, TP100.1
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
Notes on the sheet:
USB connector with protection
Programming & debug
VBUS is not connected: otherwise after enabling USB pull-up inside STM, +3v3 will present at VBUS even after cable disconnect, cauising USB_DISCONN event failure.
USB connect detector
Radio
Balun
CC Power Filter
Pins 15, 14, 11, 9, 4, 18
Matching circuit
LED ctrl
Registers' capacitors
PWR Indication LEDs
Voltage measurement dividers (20/(20+100)) = 20/120 = 1/6
Cooler control
